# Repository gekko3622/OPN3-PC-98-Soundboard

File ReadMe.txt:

___  ____  _   _ _____  __     ______    ___  
 / _ \|  _ \| \ | |___ /  \ \   / /___ \  / _ \ 
| | | | |_) |  \| | |_ \   \ \ / /  __) || | | |
| |_| |  __/| |\  |___) |   \ V /  / __/ | |_| |
 \___/|_|   |_| \_|____/     \_/  |_____(_)___/ 

PC-9801/9821 Soundboard
2024.3 by RLB (Gekko3622)
Original schematic by Ethy1ene

Intro:

This ZIP archive contains all files related to my implementation of Ethy1ene's publicly released OPN3 schematic. Please feel free to modify or improve it in any way you see fit.

------------------------------------------------------------------------------------------------------

ZIP Contents:

1. KiCAD Project - Contains the full KiCad project for my version of the OPN3 soundboard.

2. Production Files - Contains all files necessary to produce the exact PCB that I have. 
   
   I HIGHLY RECOMMEND paying your PCB fabricator to supply and assemble the small SMD devices. 
   This folder includes turnkey BOM and top placement files formatted for JLCPCB.
   
   This will include my logo on the PCB, as it is guaranteed to be an exact match to my own design.
   If you wish to produce a PCB without my logo, you will need to export new fabrication files from KiCad.

3. JEDEC File - Contains a .JED file that must be programmed to the GAL20V8.
                This is mandatory. Please ensure you have a programmer that can write to a GAL20V8.

4. DigiKey Order List - Lists all components I purchased from DigiKey. Anything not on this list was 
   purchased for assembly by JLCPCB or needed to be purchased used or new old stock (see below).

------------------------------------------------------------------------------------------------------

Used/New Old Stock Parts Required:

1. YMF288-M Sound Chip
2. NEC UPD6379GR 16-Bit DAC
3. Lattice GAL20V8B-25LP Programmable Logic Device (PLD)

Note 1: UPD6379A is a pin-reversed variant. If you use it for some reason, it needs to be rotated 180 degrees.
Note 2: National Semiconductor makes a GAL20V8 which is still available. I have not tested it and cannot tell you which part number would be the best match.

------------------------------------------------------------------------------------------------------

Credits:

HUGE thanks to Ethy1ene for releasing his original OPN3 soundboard schematic and providing advice and troubleshooting. Without his help, this project wouldn't exist.

Thanks also to TD-Linux and i509VCB for their advice and guidance, pushing me to learn better practices as I worked.

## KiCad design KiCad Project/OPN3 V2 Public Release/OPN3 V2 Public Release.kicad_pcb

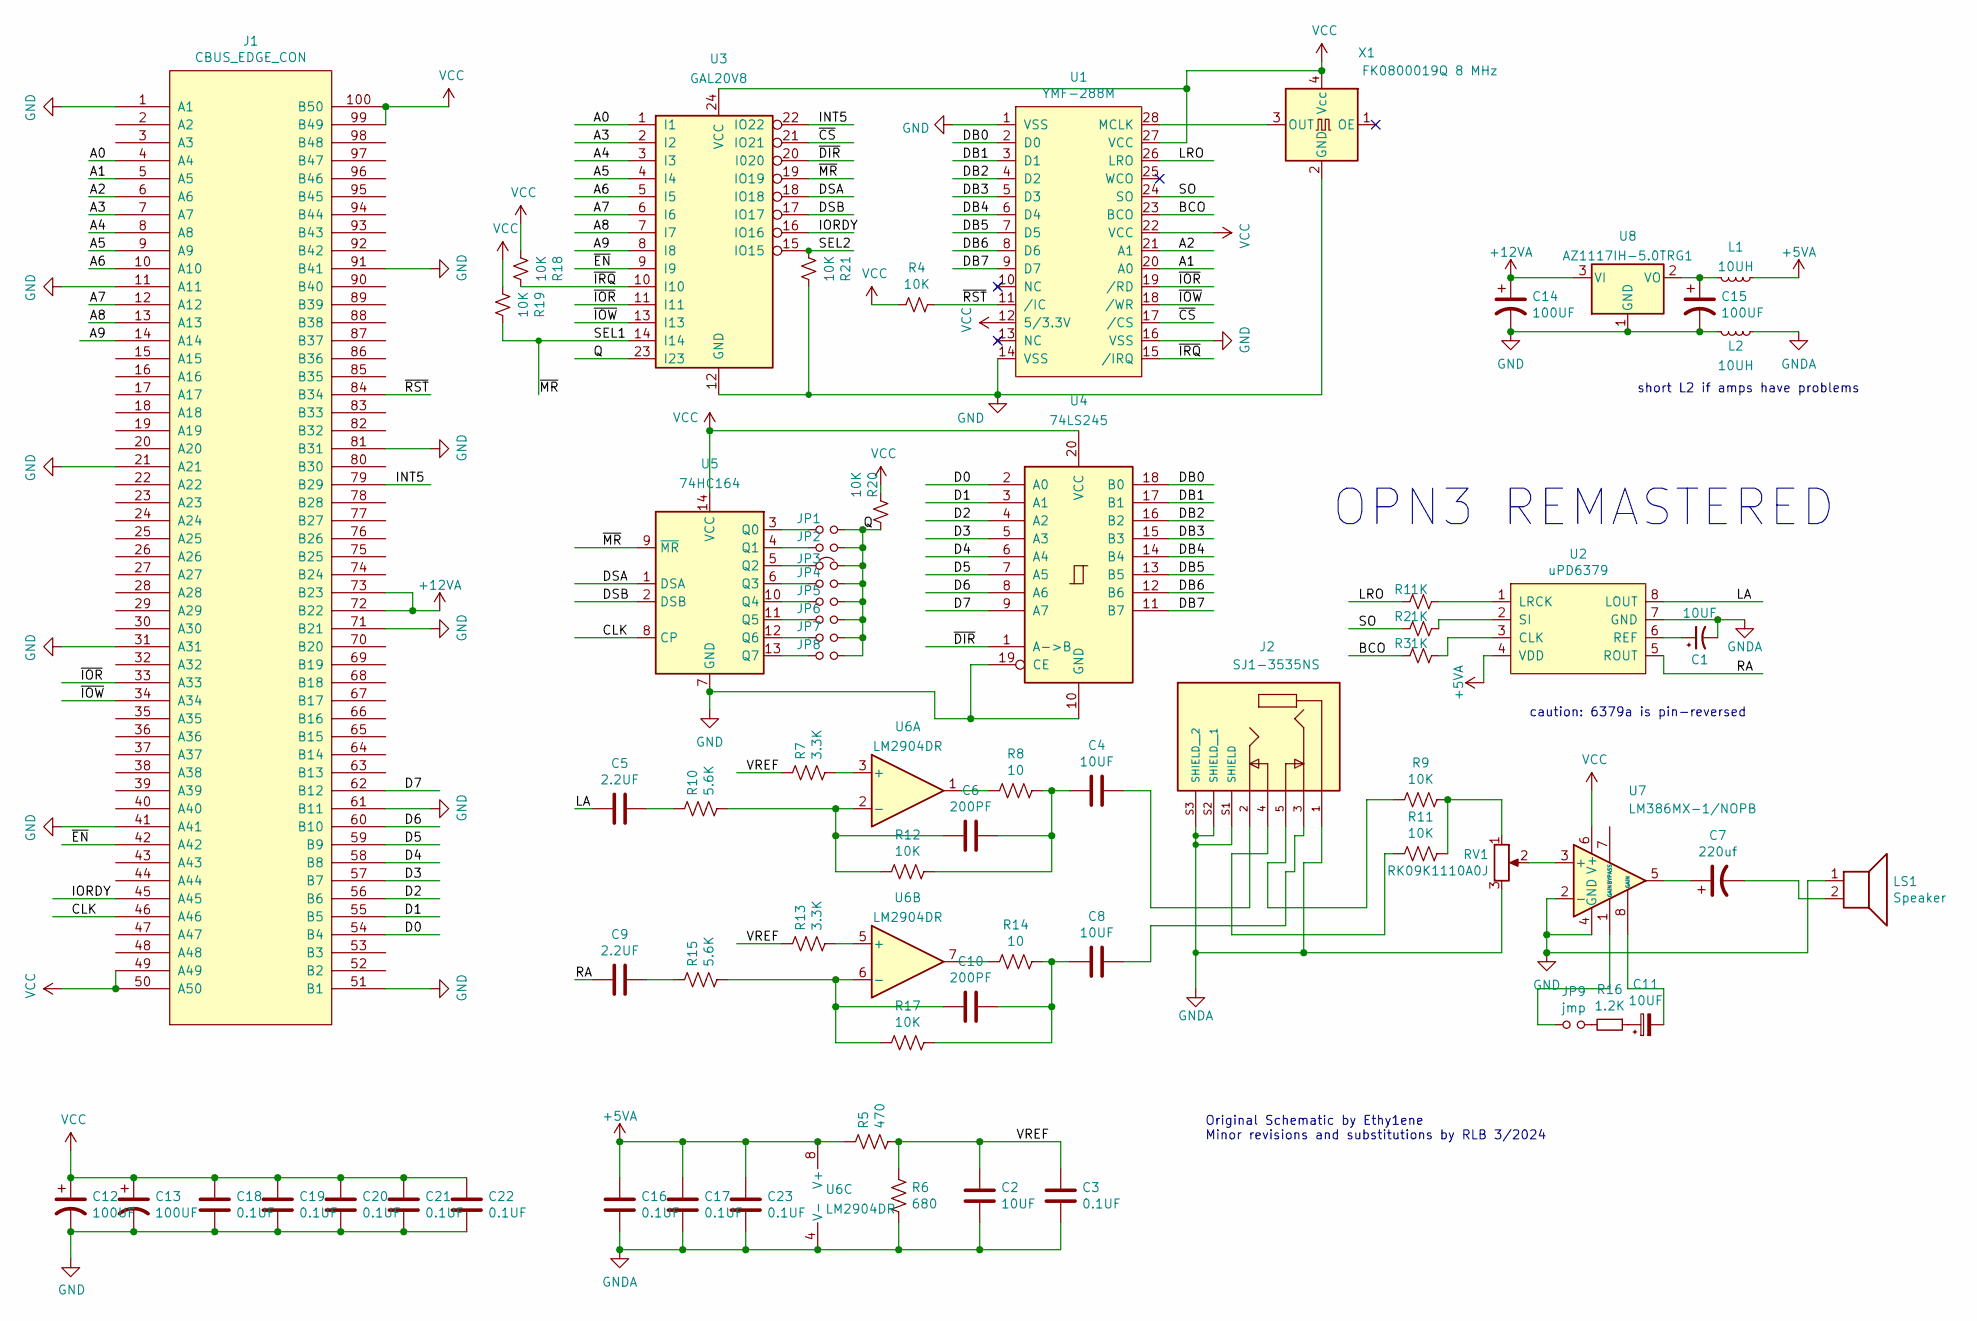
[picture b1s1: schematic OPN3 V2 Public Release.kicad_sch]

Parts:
C1: 10UF; CP_EIA-3216-18_Kemet-A
C2, C4, C8: 10UF; C_0603_1608Metric
C3, C16, C17, C18, C19, C20, C21, C22, C23: 0.1UF; C_0603_1608Metric
C5, C9: 2.2UF; C_0603_1608Metric
C6, C10: 200PF; C_0603_1608Metric
C7: 220uf; CP_Radial_D5.0mm_P2.50mm
C11: 10UF; CP_Radial_D6.3mm_P2.50mm
C12, C13, C14, C15: 100UF; CP_Radial_D6.3mm_P2.50mm
J1: CBUS_EDGE_CON; PC-98 CBus Pads 1-100
J2: SJ1-3535NS; CUI_SJ1-3535NS
JP1, JP2, JP4, JP5, JP6, JP7, JP8: Jumper_NO_Small; SolderJumper-2_P1.3mm_Open_Pad1.0x1.5mm
JP3: W; SolderJumper-2_P1.3mm_Bridged_Pad1.0x1.5mm
JP9: jmp; SolderJumper-2_P1.3mm_Open_Pad1.0x1.5mm
L1, L2: 10UH; L_1206_3216Metric
LS1: Speaker; PinHeader_1x02_P2.54mm_Vertical
R1, R2, R3: 1K; R_0603_1608Metric
R4, R9, R11, R12, R17, R18, R19, R20, R21: 10K; R_0603_1608Metric
R5: 470; R_0603_1608Metric
R6: 680; R_0603_1608Metric
R7, R13: 3.3K; R_0603_1608Metric
R8, R14: 10; R_0603_1608Metric
R10, R15: 5.6K; R_0603_1608Metric
R16: 1.2K; R_0603_1608Metric
RV1: RK09K1110A0J; Potentiometer_Alps_RK09K_Single_Horizontal; Part# ALPS RK09K1110B1R
U1: YMF-288M; YMF288-M; DigiKey Link None, source used/new old stock
U2: uPD6379; SOIC-8_5.23x5.23mm_P1.27mm; DigiKey Link None, source used/new old stock
U3: GAL20V8; DIP-24_W7.62mm
U4: 74LS245; SO-20_5.3x12.6mm_P1.27mm
U5: 74HC164; SO-14_5.3x10.2mm_P1.27mm
U6: LM2904DR; SOIC-8_5.23x5.23mm_P1.27mm
U7: LM386MX-1/NOPB; SOIC-8_5.23x5.23mm_P1.27mm
U8: AZ1117IH-5.0TRG1; SOT-223-3_TabPin2
X1: FK0800019Q 8 MHz; Oscillator_SMD_SeikoEpson_SG8002CE-4Pin_3.2x2.5mm_HandSolde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

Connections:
+5VA: C16.1, C17.1, C23.1, L1.2, R5.1, U2.4 (VDD), U6.8 (V+)
+12VA: C14.1, J1.72 (B22), J1.73 (B23), U8.3 (VI)
/A0: J1.4 (A4), U3.1 (I1)
/A1: J1.5 (A5), U1.20 (A0)
/A2: J1.6 (A6), U1.21 (A1)
/A3: J1.7 (A7), U3.2 (I2)
/A4: J1.8 (A8), U3.3 (I3)
/A5: J1.9 (A9), U3.4 (I4)
/A6: J1.10 (A10), U3.5 (I5)
/A7: J1.12 (A12), U3.6 (I6)
/A8: J1.13 (A13), U3.7 (I7)
/A9: J1.14 (A14), U3.8 (I8)
/BCO: R3.1, U1.23 (BCO)
/CLK: J1.46 (A46), U5.8 (CP)
/D0: J1.54 (B4), U4.2 (A0)
/D1: J1.55 (B5), U4.3 (A1)
/D2: J1.56 (B6), U4.4 (A2)
/D3: J1.57 (B7), U4.5 (A3)
/D4: J1.58 (B8), U4.6 (A4)
/D5: J1.59 (B9), U4.7 (A5)
/D6: J1.60 (B10), U4.8 (A6)
/D7: J1.62 (B12), U4.9 (A7)
/DB0: U1.2 (D0), U4.18 (B0)
/DB1: U1.3 (D1), U4.17 (B1)
/DB2: U1.4 (D2), U4.16 (B2)
/DB3: U1.5 (D3), U4.15 (B3)
/DB4: U1.6 (D4), U4.14 (B4)
/DB5: U1.7 (D5), U4.13 (B5)
/DB6: U1.8 (D6), U4.12 (B6)
/DB7: U1.9 (D7), U4.11 (B7)
/DSA: U3.18 (IO18), U5.1 (DSA)
/DSB: U3.17 (IO17), U5.2 (DSB)
/INT5: J1.79 (B29), U3.22 (IO22)
/IORDY: J1.45 (A45), U3.16 (IO16)
/LA: C5.1, U2.8 (LOUT)
/LRO: R1.1, U1.26 (LRO)
/Q: JP1.2, JP2.2, JP3.2, JP4.2, JP5.2, JP6.2, JP7.2, JP8.2, R20.1, U3.23 (I23)
/RA: C9.1, U2.5 (ROUT)
/SEL1: R19.1, U3.14 (I14), U3.19 (IO19), U5.9 (~MR)
/SEL2: R21.2, U3.15 (IO15)
/SO: R2.1, U1.24 (SO)
/VREF: C2.1, C3.1, R5.2, R6.1, R7.1, R13.1
/~CS: U1.17 (/CS), U3.21 (IO21)
/~DIR: U3.20 (I020), U4.1 (A->B)
/~EN: J1.42 (A42), U3.9 (I9)
/~IOR: J1.33 (A33), U1.19 (/RD), U3.11 (I11)
/~IOW: J1.34 (A34), U1.18 (/WR), U3.13 (I13)
/~IRQ: R18.1, U1.15 (/IRQ), U3.10 (I10)
/~RST: J1.84 (B34), R4.1, U1.11 (/IC)
GND: C12.2, C13.2, C14.2, C15.2, C18.2, C19.2, C20.2, C21.2, C22.2, J1.1 (A1), J1.11 (A11), J1.21 (A21), J1.31 (A31), J1.41 (A41), J1.51 (B1), J1.61 (B11), J1.71 (B21), J1.81 (B31), J1.91 (B41), L2.1, LS1.1, R21.1, U1.1 (VSS), U1.14 (VSS), U1.16 (VSS), U3.12 (GND), U4.10 (GND), U4.19 (CE), U5.7 (GND), U7.2 (-), U7.4 (GND), U8.1 (GND), X1.2 (GND)
GNDA: C1.2, C2.2, C3.2, C16.2, C17.2, C23.2, J2.1, J2.S1 (SHIELD), J2.S2 (SHIELD__1), J2.S3 (SHIELD__2), L2.2, R6.2, RV1.3, U2.7 (GND), U6.4 (V-)
unnamed: C4.1, J2.2
unnamed: C4.2, C6.1, R8.1, R12.1
unnamed: C5.2, R10.1
unnamed: C7.1, U7.5
unnamed: C7.2, LS1.2
unnamed: C8.1, J2.3
unnamed: C9.2, R15.1
unnamed: C8.2, C10.1, R14.1, R17.1
unnamed: C11.1, R16.1
unnamed: C11.2, U7.8 (GAIN)
unnamed: J2.4, R11.2
unnamed: J2.5, R9.2
unnamed: JP9.1, U7.1 (GAIN)
unnamed: JP9.2, R16.2
unnamed: R8.2, U6.1
unnamed: R9.1, R11.1, RV1.1
unnamed: R14.2, U6.7
unnamed: U1.28 (MCLK), X1.3 (OUT)
unnamed: R3.2, U2.3 (CLK)
unnamed: R1.2, U2.1 (LRCK)
unnamed: C1.1, U2.6 (REF)
unnamed: R2.2, U2.2 (SI)
unnamed: JP1.1, U5.3 (Q0)
unnamed: JP2.1, U5.4 (Q1)
unnamed: JP3.1, U5.5 (Q2)
unnamed: JP4.1, U5.6 (Q3)
unnamed: JP5.1, U5.10 (Q4)
unnamed: JP6.1, U5.11 (Q5)
unnamed: JP7.1, U5.12 (Q6)
unnamed: JP8.1, U5.13 (Q7)
unnamed: R7.2, U6.3 (+)
unnamed: C6.2, R10.2, R12.2, U6.2 (-)
unnamed: R13.2, U6.5 (+)
unnamed: C10.2, R15.2, R17.2, U6.6 (-)
unnamed: RV1.2, U7.3 (+)
unnamed: C15.1, L1.1, U8.2 (VO)
VCC: C12.1, C13.1, C18.1, C19.1, C20.1, C21.1, C22.1, J1.49 (A49), J1.50 (A50), J1.99 (B49), J1.100 (B50), R4.2, R18.2, R19.2, R20.2, U1.12 (5/3.3V), U1.22 (VCC), U1.27 (VCC), U3.24 (VCC), U4.20 (VCC), U5.14 (VCC), U7.6 (V+), X1.4 (Vcc)

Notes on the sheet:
Original Schematic by Ethy1ene Minor revisions and substitutions by RLB 3/2024
OPN3 REMASTERED
caution: 6379a is pin-reversed
short L2 if amps have problems

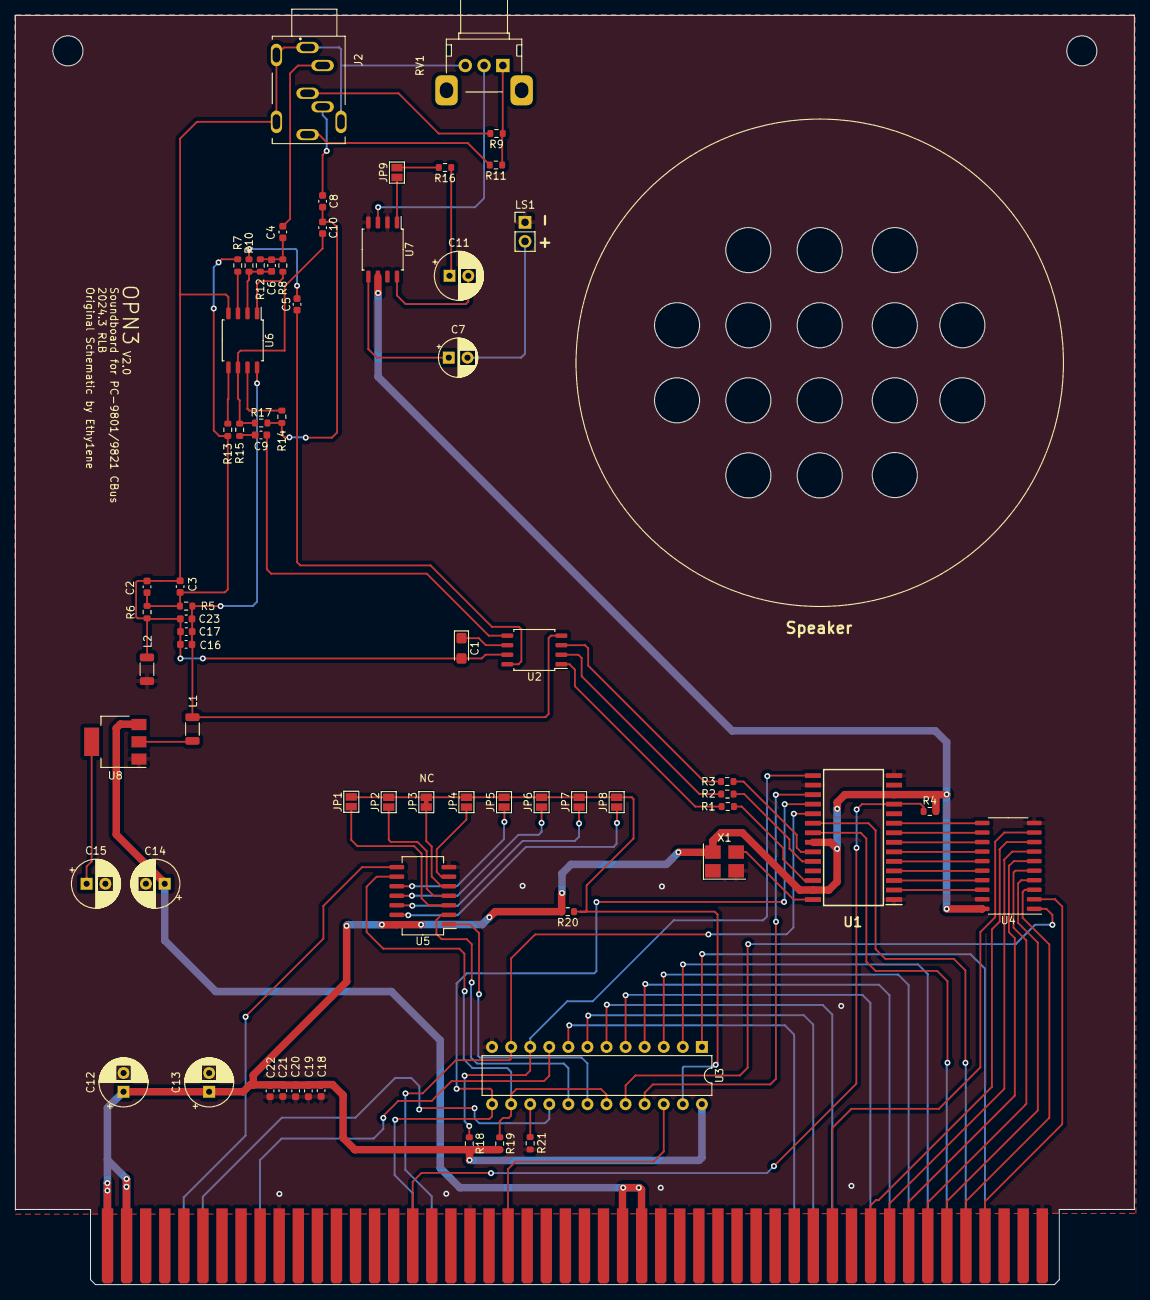
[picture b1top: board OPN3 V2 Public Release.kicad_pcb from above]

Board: 2 copper layers, 149.0 x 169.0 mm, 68 parts (0 on the bottom side), 88 nets.

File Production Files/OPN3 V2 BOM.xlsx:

Comment | Designator | Footprint | Quantity | JLCPCB Part #（optional）
10UF | C1 | Capacitor_Tantalum_SMD:CP_EIA-3216-18_Kemet-A | 1 | Basic C7171
10UF | C2, C4, C8 | Capacitor_SMD:C_0603_1608Metric | 3 | Basic C96446
0.1UF | C3, C16, C17, C18, C19, C20, C21, C22, C23 | Capacitor_SMD:C_0603_1608Metric | 9 | Basic C14663
2.2UF | C5, C9 | Capacitor_SMD:C_0603_1608Metric | 2 | Basic C23630
200PF | C6, C10 | Capacitor_SMD:C_0603_1608Metric | 2 | Extended C113796
10UH | L1, L2 | Inductor_SMD:L_1206_3216Metric | 2 | Extended C1051
1K | R1, R2, R3 | Resistor_SMD:R_0603_1608Metric | 3 | Basic C21190
10K | R4, R9, R11, R12, R17, R18, R19, R20, R21 | Resistor_SMD:R_0603_1608Metric | 9 | Basic C25804
470 | R5 | Resistor_SMD:R_0603_1608Metric | 1 | Basic C23179
680 | R6 | Resistor_SMD:R_0603_1608Metric | 1 | Basic C23228
3.3K | R7, R13 | Resistor_SMD:R_0603_1608Metric | 2 | Basic C22978
10 | R8, R14 | Resistor_SMD:R_0603_1608Metric | 2 | Basic C22859
5.6K | R10, R15 | Resistor_SMD:R_0603_1608Metric | 2 | Basic C23189
1.2K | R16 | Resistor_SMD:R_0603_1608Metric | 1 | Basic C22765

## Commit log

2024-04-07 Delete OPN3 V2 Public Release.zip
    File was redundant
2024-04-07 Added License
